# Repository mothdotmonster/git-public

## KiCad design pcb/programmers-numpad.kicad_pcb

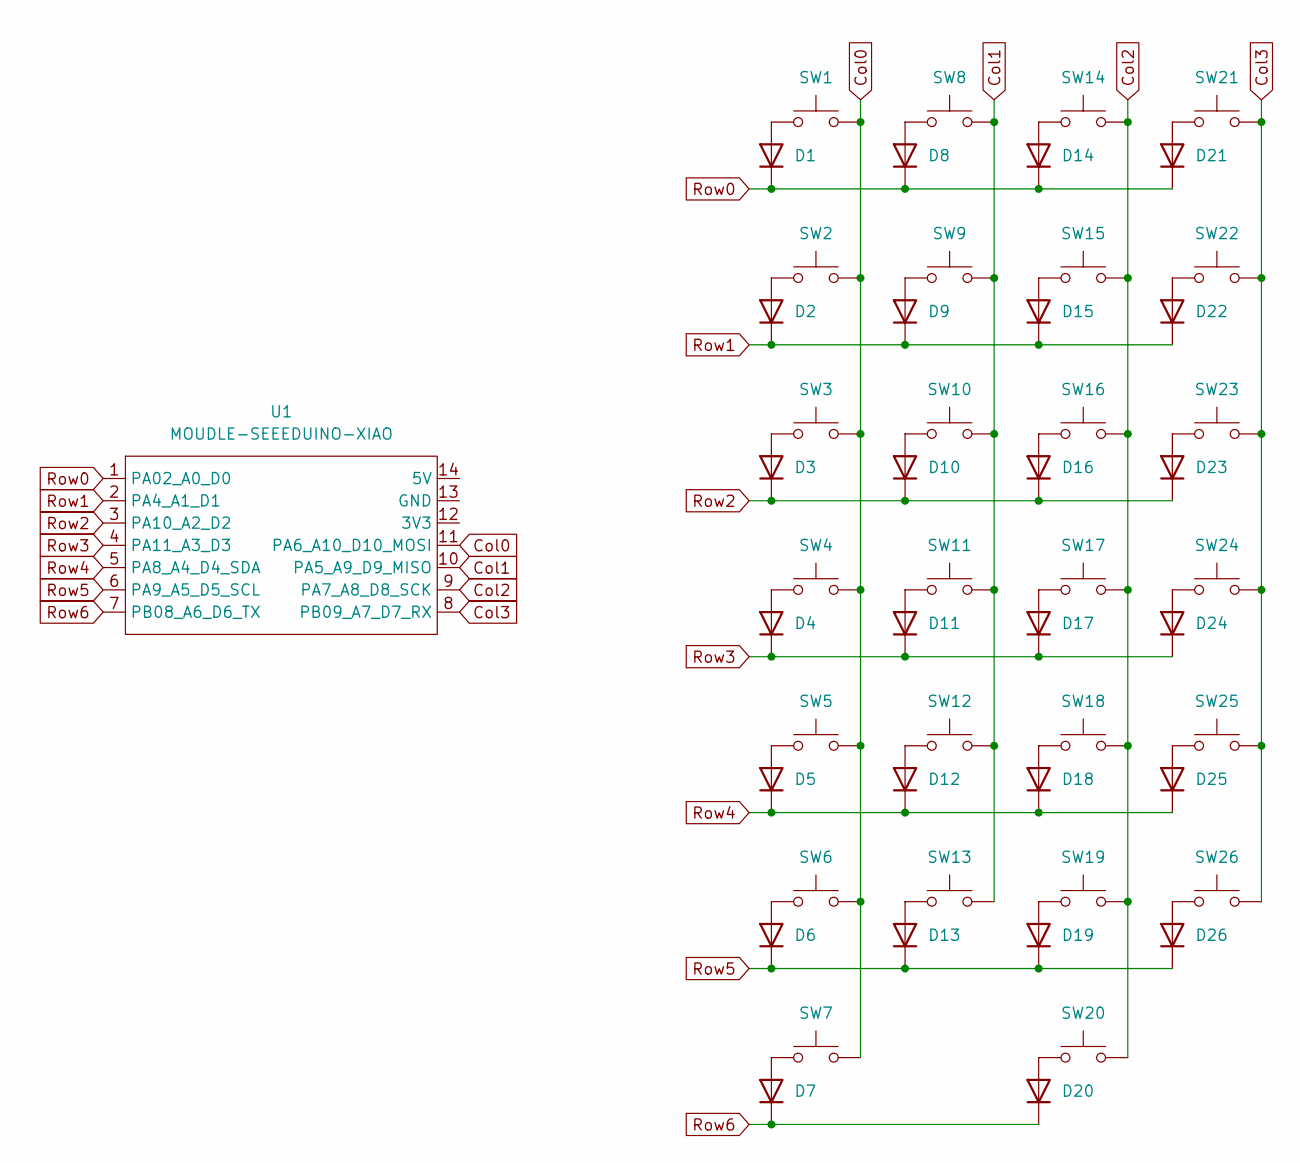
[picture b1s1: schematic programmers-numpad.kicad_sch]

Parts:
D1, D2, D3, D4, D5, D6, D7, D8, D9, D10, D11, D12, D13, D14, D15, D16, D17, D18, D19, D20, D21, D22, D23, D24, D25, D26: D; D_SOD-323; JLC C2128
SW1, SW2, SW3, SW4, SW5, SW6, SW7, SW8, SW9, SW10, SW11, SW12, SW13, SW14, SW15, SW16, SW17, SW18, SW19, SW20, SW21, SW22, SW23, SW24, SW25, SW26: SW_Push; SW_Cherry_MX_PCB_1.00u
U1: MOUDLE-SEEEDUINO-XIAO; MOUDLE14P-SMD-2.54-21X17.8MM

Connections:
Col0: SW1.2, SW2.2, SW3.2, SW4.2, SW5.2, SW6.2, SW7.2, U1.11 (PA6_A10_D10_MOSI)
Col1: SW8.2, SW9.2, SW10.2, SW11.2, SW12.2, SW13.2, U1.10 (PA5_A9_D9_MISO)
Col2: SW14.2, SW15.2, SW16.2, SW17.2, SW18.2, SW19.2, SW20.2, U1.9 (PA7_A8_D8_SCK)
Col3: SW21.2, SW22.2, SW23.2, SW24.2, SW25.2, SW26.2, U1.8 (PB09_A7_D7_RX)
unnamed: D1.2 (A), SW1.1
unnamed: D2.2 (A), SW2.1
unnamed: D3.2 (A), SW3.1
unnamed: D4.2 (A), SW4.1
unnamed: D5.2 (A), SW5.1
unnamed: D6.2 (A), SW6.1
unnamed: D7.2 (A), SW7.1
unnamed: D8.2 (A), SW8.1
unnamed: D9.2 (A), SW9.1
unnamed: D10.2 (A), SW10.1
unnamed: D11.2 (A), SW11.1
unnamed: D12.2 (A), SW12.1
unnamed: D13.2 (A), SW13.1
unnamed: D14.2 (A), SW14.1
unnamed: D15.2 (A), SW15.1
unnamed: D16.2 (A), SW16.1
unnamed: D17.2 (A), SW17.1
unnamed: D18.2 (A), SW18.1
unnamed: D19.2 (A), SW19.1
unnamed: D20.2 (A), SW20.1
unnamed: D21.2 (A), SW21.1
unnamed: D22.2 (A), SW22.1
unnamed: D23.2 (A), SW23.1
unnamed: D24.2 (A), SW24.1
unnamed: D25.2 (A), SW25.1
unnamed: D26.2 (A), SW26.1
Row0: D1.1 (K), D8.1 (K), D14.1 (K), D21.1 (K), U1.1 (PA02_A0_D0)
Row1: D2.1 (K), D9.1 (K), D15.1 (K), D22.1 (K), U1.2 (PA4_A1_D1)
Row2: D3.1 (K), D10.1 (K), D16.1 (K), D23.1 (K), U1.3 (PA10_A2_D2)
Row3: D4.1 (K), D11.1 (K), D17.1 (K), D24.1 (K), U1.4 (PA11_A3_D3)
Row4: D5.1 (K), D12.1 (K), D18.1 (K), D25.1 (K), U1.5 (PA8_A4_D4_SDA)
Row5: D6.1 (K), D13.1 (K), D19.1 (K), D26.1 (K), U1.6 (PA9_A5_D5_SCL)
Row6: D7.1 (K), D20.1 (K), U1.7 (PB08_A6_D6_TX)

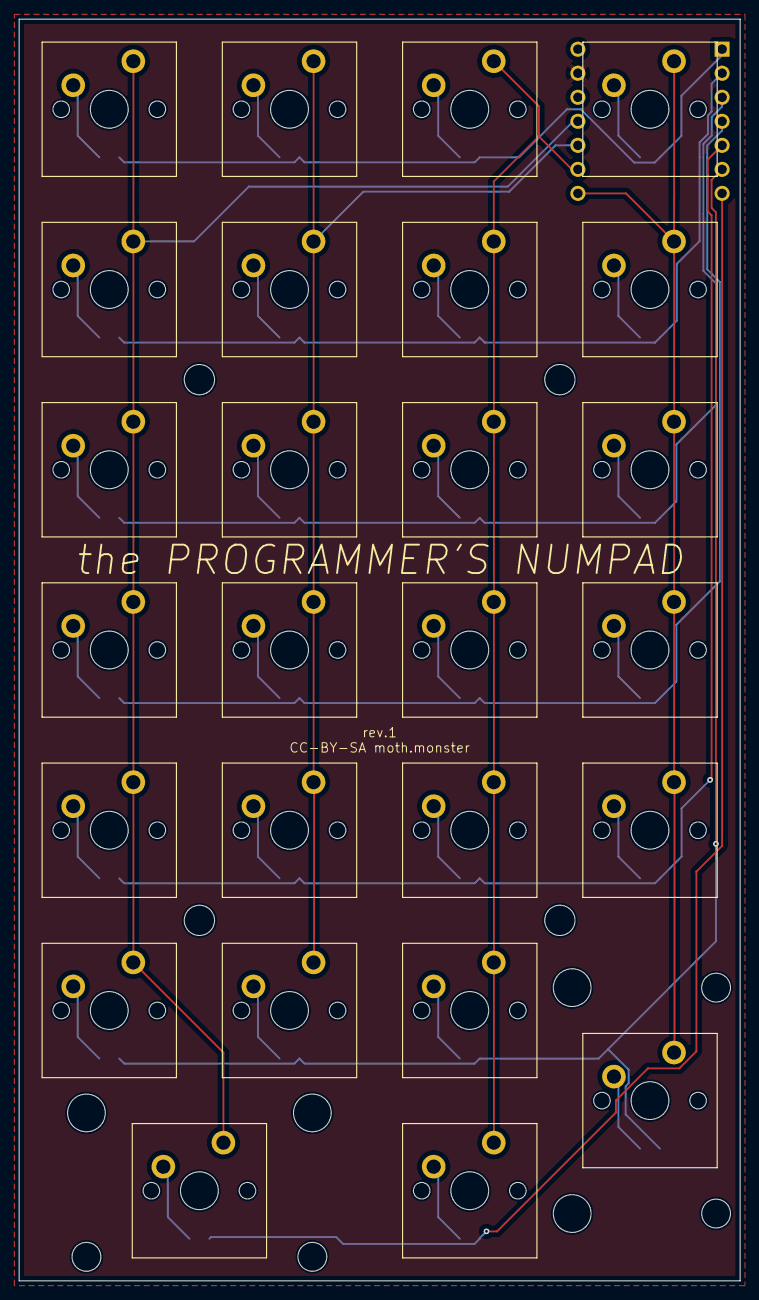
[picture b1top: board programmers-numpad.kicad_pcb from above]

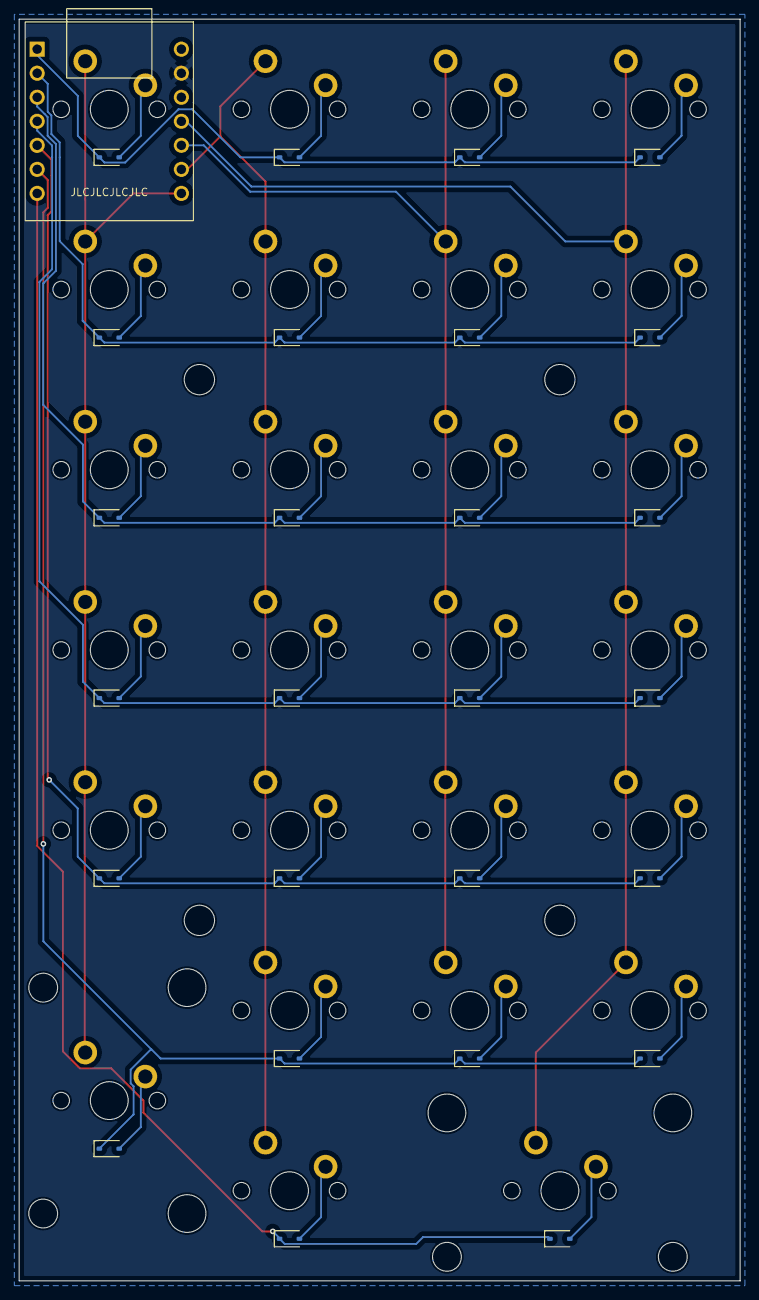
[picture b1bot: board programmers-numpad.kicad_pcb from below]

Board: 2 copper layers, 76.2 x 133.4 mm, 55 parts (27 on the bottom side), 37 nets.

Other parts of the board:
REF1**, REF2: MountingHole_3.2mm_M3

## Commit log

2024-06-27 initial commit - rev.1
2024-06-27 organize
2024-06-27 initial readme
2024-06-27 add case files
2024-06-27 orient case parts
2024-06-27 add firmware
2024-06-27 add firmware tips
2024-06-27 formatting
2024-06-27 thiucken bottom pegs
2024-06-27 add links

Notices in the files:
pcb/programmers-numpad.kicad_pcb:
CC-BY-SA moth.monster
